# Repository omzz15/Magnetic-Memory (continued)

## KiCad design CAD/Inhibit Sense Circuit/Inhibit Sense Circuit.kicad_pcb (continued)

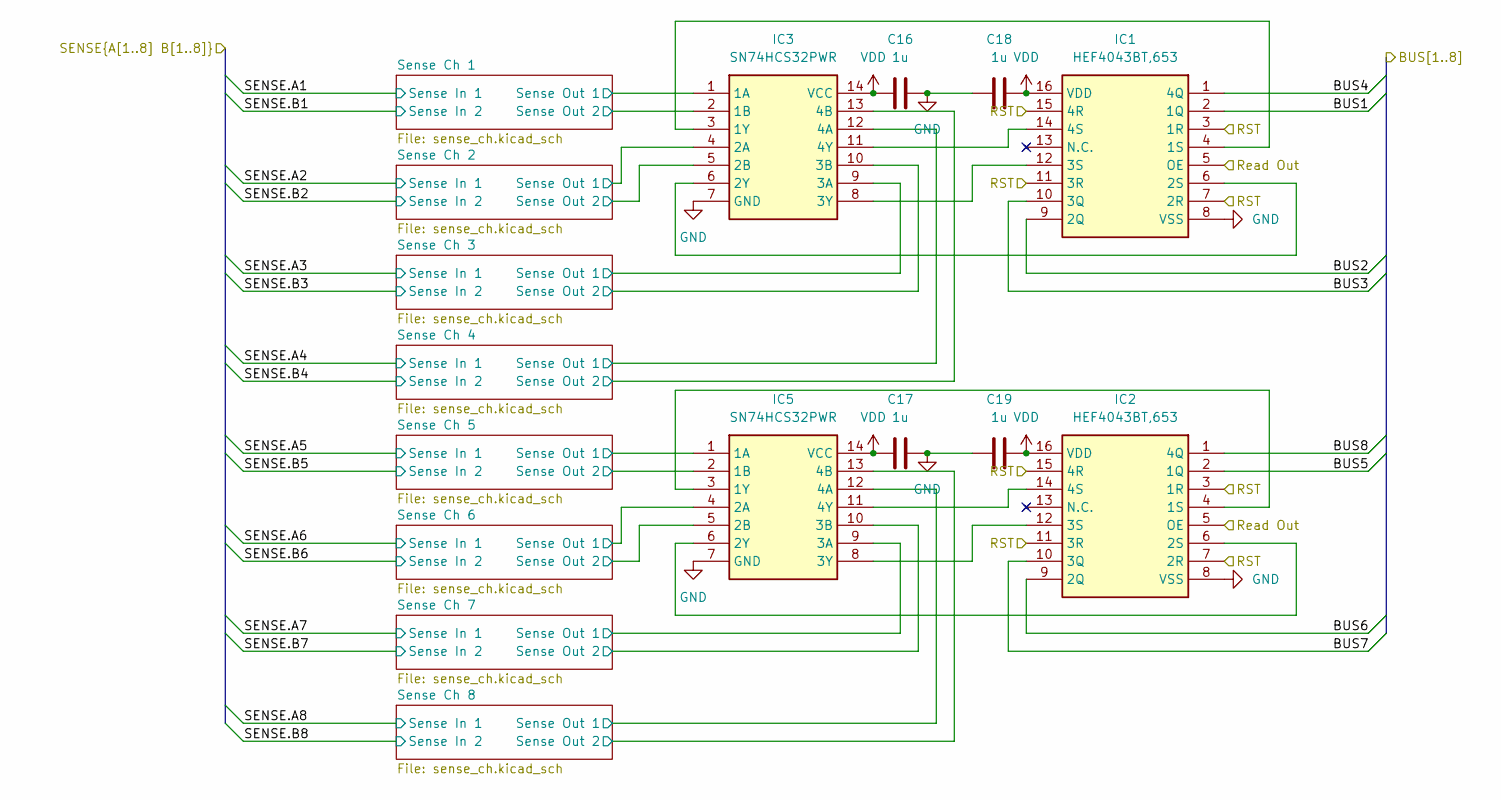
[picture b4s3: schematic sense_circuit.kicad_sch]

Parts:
C16, C17, C18, C19: 1u; C_0603_1608Metric_Pad1.08x0.95mm_HandSolder
IC1, IC2: HEF4043BT,653; HEF4043BT653; Mouser Part Number 771-HEF4043BT653
IC3, IC5: SN74HCS32PWR; SOP65P640X120-14N; Mouser Part Number 595-SN74HCS32PWR

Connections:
/BUS1: IC1.2 (1Q); also elsewhere on the board
/BUS2: IC1.9 (2Q); also elsewhere on the board
/BUS3: IC1.10 (3Q); also elsewhere on the board
/BUS4: IC1.1 (4Q); also elsewhere on the board
/BUS5: IC2.2 (1Q); also elsewhere on the board
/BUS6: IC2.9 (2Q); also elsewhere on the board
/BUS7: IC2.10 (3Q); also elsewhere on the board
/BUS8: IC2.1 (4Q); also elsewhere on the board
/RST: IC1.3 (1R), IC1.7 (2R), IC1.11 (3R), IC1.15 (4R), IC2.3 (1R), IC2.7 (2R), IC2.11 (3R), IC2.15 (4R); also elsewhere on the board
/Read Out: IC1.5 (OE), IC2.5 (OE); also elsewhere on the board
/Sense Circuit/Sense Ch 1/Sense Out 1: IC3.1 (1A); also elsewhere on the board
/Sense Circuit/Sense Ch 1/Sense Out 2: IC3.2 (1B); also elsewhere on the board
/Sense Circuit/Sense Ch 2/Sense Out 1: IC3.4 (2A); also elsewhere on the board
/Sense Circuit/Sense Ch 2/Sense Out 2: IC3.5 (2B); also elsewhere on the board
/Sense Circuit/Sense Ch 3/Sense Out 1: IC3.9 (3A); also elsewhere on the board
/Sense Circuit/Sense Ch 3/Sense Out 2: IC3.10 (3B); also elsewhere on the board
/Sense Circuit/Sense Ch 4/Sense Out 1: IC3.12 (4A); also elsewhere on the board
/Sense Circuit/Sense Ch 4/Sense Out 2: IC3.13 (4B); also elsewhere on the board
/Sense Circuit/Sense Ch 5/Sense Out 1: IC5.1 (1A); also elsewhere on the board
/Sense Circuit/Sense Ch 5/Sense Out 2: IC5.2 (1B); also elsewhere on the board
/Sense Circuit/Sense Ch 6/Sense Out 1: IC5.4 (2A); also elsewhere on the board
/Sense Circuit/Sense Ch 6/Sense Out 2: IC5.5 (2B); also elsewhere on the board
/Sense Circuit/Sense Ch 7/Sense Out 1: IC5.9 (3A); also elsewhere on the board
/Sense Circuit/Sense Ch 7/Sense Out 2: IC5.10 (3B); also elsewhere on the board
/Sense Circuit/Sense Ch 8/Sense Out 1: IC5.12 (4A); also elsewhere on the board
/Sense Circuit/Sense Ch 8/Sense Out 2: IC5.13 (4B); also elsewhere on the board
GND: C16.2, C17.2, C18.1, C19.1, IC1.8 (VSS), IC2.8 (VSS), IC3.7 (GND), IC5.7 (GND); also elsewhere on the board
unnamed: IC1.4 (1S), IC3.3 (1Y)
unnamed: IC1.6 (2S), IC3.6 (2Y)
unnamed: IC1.12 (3S), IC3.8 (3Y)
unnamed: IC1.14 (4S), IC3.11 (4Y)
unnamed: IC2.4 (1S), IC5.3 (1Y)
unnamed: IC2.6 (2S), IC5.6 (2Y)
unnamed: IC2.12 (3S), IC5.8 (3Y)
unnamed: IC2.14 (4S), IC5.11 (4Y)
VDD: C16.1, C17.1, C18.2, C19.2, IC1.16 (VDD), IC2.16 (VDD), IC3.14 (VCC), IC5.14 (VCC); also elsewhere on the board

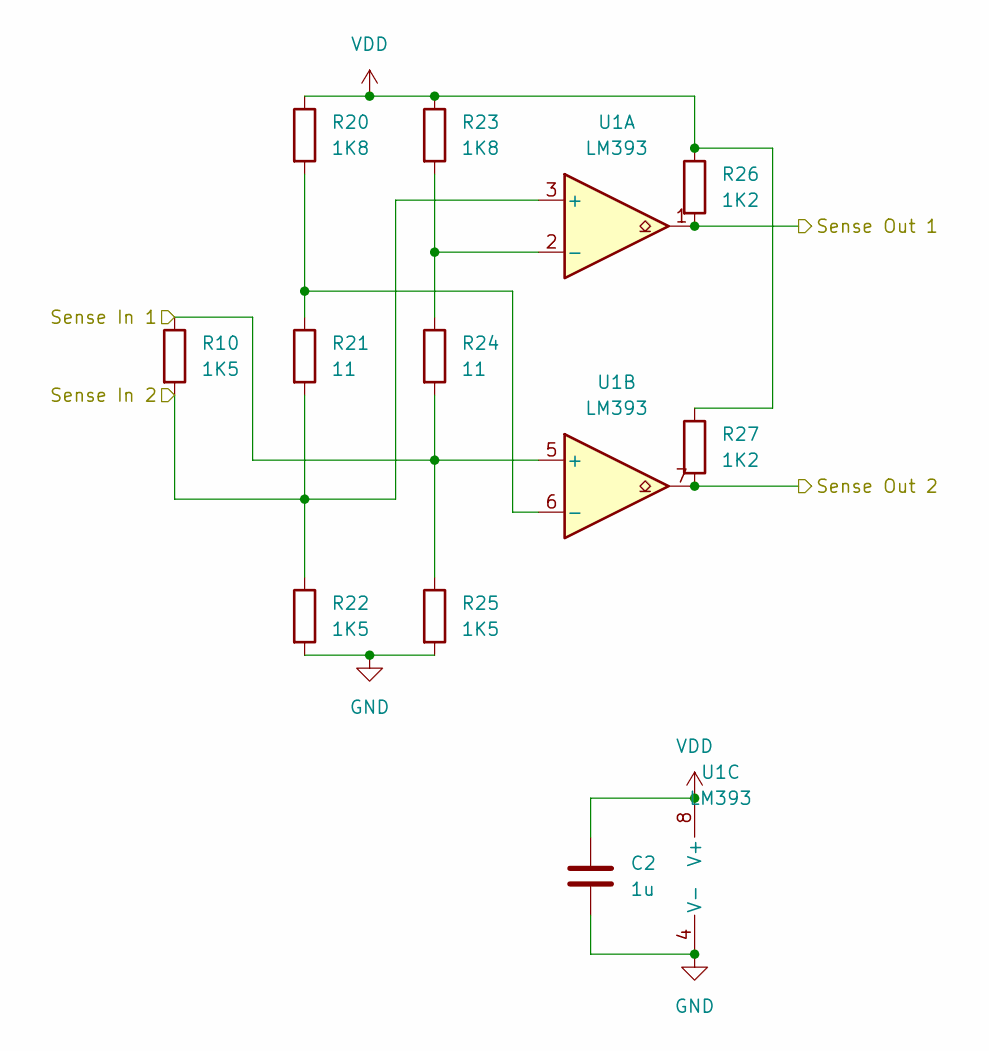
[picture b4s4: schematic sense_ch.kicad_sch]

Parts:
C2: 1u; C_0603_1608Metric_Pad1.08x0.95mm_HandSolder
R10, R22, R25: 1K5; R_0603_1608Metric_Pad0.98x0.95mm_HandSolder
R20, R23: 1K8; R_0603_1608Metric_Pad0.98x0.95mm_HandSolder
R21, R24: 11; R_0603_1608Metric_Pad0.98x0.95mm_HandSolder
R26, R27: 1K2; R_0603_1608Metric_Pad0.98x0.95mm_HandSolder
U1: LM393; SO1SOP-8-A_TPK

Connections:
/IS_LINES.A1: R10.1, R24.2, R25.1, U1.5 (+); also elsewhere on the board
/IS_LINES.B1: R10.2, R21.2, R22.1, U1.3 (+); also elsewhere on the board
/Sense Circuit/Sense Ch 1/Sense Out 1: R26.2, U1.1; also elsewhere on the board
/Sense Circuit/Sense Ch 1/Sense Out 2: R27.2, U1.7; also elsewhere on the board
GND: C2.2, R22.2, R25.2, U1.4 (V-); also elsewhere on the board
unnamed: R23.2, R24.1, U1.2 (-)
unnamed: R20.2, R21.1, U1.6 (-)
VDD: C2.1, R20.1, R23.1, R26.1, R27.1, U1.8 (V+); also elsewhere on the board

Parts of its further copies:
C1, C3, C4, C5, C6, C7, C8: 1u; C_0603_1608Metric_Pad1.08x0.95mm_HandSolder
R9, R13, R16, R19, R28, R31, R34, R37, R41, R47, R53, R57, R60, R63, R66, R69, R72, R75, R78, R83, R86: 1K5; R_0603_1608Metric_Pad0.98x0.95mm_HandSolder
R11, R14, R29, R32, R38, R43, R55, R58, R64, R67, R73, R76, R81, R84: 1K8; R_0603_1608Metric_Pad0.98x0.95mm_HandSolder
R12, R15, R30, R33, R39, R45, R56, R59, R65, R68, R74, R77, R82, R85: 11; R_0603_1608Metric_Pad0.98x0.95mm_HandSolder
R17, R18, R35, R36, R49, R51, R61, R62, R70, R71, R79, R80, R87, R88: 1K2; R_0603_1608Metric_Pad0.98x0.95mm_HandSolder
U2, U3, U4, U5, U6, U7, U8: LM393; SO1SOP-8-A_TPK

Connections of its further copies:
/IS_LINES.A2: R9.1, R15.2, R16.1, U2.5 (+); also elsewhere on the board
/IS_LINES.A3: R19.1, R33.2, R34.1, U3.5 (+); also elsewhere on the board
/IS_LINES.A4: R28.1, R45.2, R47.1, U4.5 (+); also elsewhere on the board
/IS_LINES.A5: R37.1, R59.2, R60.1, U5.5 (+); also elsewhere on the board
/IS_LINES.A6: R53.1, R68.2, R69.1, U6.5 (+); also elsewhere on the board
/IS_LINES.A7: R63.1, R77.2, R78.1, U7.5 (+); also elsewhere on the board
/IS_LINES.A8: R72.1, R85.2, R86.1, U8.5 (+); also elsewhere on the board
/IS_LINES.B2: R9.2, R12.2, R13.1, U2.3 (+); also elsewhere on the board
/IS_LINES.B3: R19.2, R30.2, R31.1, U3.3 (+); also elsewhere on the board
/IS_LINES.B4: R28.2, R39.2, R41.1, U4.3 (+); also elsewhere on the board
/IS_LINES.B5: R37.2, R56.2, R57.1, U5.3 (+); also elsewhere on the board
/IS_LINES.B6: R53.2, R65.2, R66.1, U6.3 (+); also elsewhere on the board
/IS_LINES.B7: R63.2, R74.2, R75.1, U7.3 (+); also elsewhere on the board
/IS_LINES.B8: R72.2, R82.2, R83.1, U8.3 (+); also elsewhere on the board
/Sense Circuit/Sense Ch 2/Sense Out 1: R17.2, U2.1; also elsewhere on the board
/Sense Circuit/Sense Ch 2/Sense Out 2: R18.2, U2.7; also elsewhere on the board
/Sense Circuit/Sense Ch 3/Sense Out 1: R35.2, U3.1; also elsewhere on the board
/Sense Circuit/Sense Ch 3/Sense Out 2: R36.2, U3.7; also elsewhere on the board
/Sense Circuit/Sense Ch 4/Sense Out 1: R49.2, U4.1; also elsewhere on the board
/Sense Circuit/Sense Ch 4/Sense Out 2: R51.2, U4.7; also elsewhere on the board
/Sense Circuit/Sense Ch 5/Sense Out 1: R61.2, U5.1; also elsewhere on the board
/Sense Circuit/Sense Ch 5/Sense Out 2: R62.2, U5.7; also elsewhere on the board
/Sense Circuit/Sense Ch 6/Sense Out 1: R70.2, U6.1; also elsewhere on the board
/Sense Circuit/Sense Ch 6/Sense Out 2: R71.2, U6.7; also elsewhere on the board
/Sense Circuit/Sense Ch 7/Sense Out 1: R79.2, U7.1; also elsewhere on the board
/Sense Circuit/Sense Ch 7/Sense Out 2: R80.2, U7.7; also elsewhere on the board
/Sense Circuit/Sense Ch 8/Sense Out 1: R87.2, U8.1; also elsewhere on the board
/Sense Circuit/Sense Ch 8/Sense Out 2: R88.2, U8.7; also elsewhere on the board
GND: C1.2, C3.2, C4.2, C5.2, C6.2, C7.2, C8.2, R13.2, R16.2, R31.2, R34.2, R41.2, R47.2, R57.2, R60.2, R66.2, R69.2, R75.2, R78.2, R83.2, R86.2, U2.4 (V-), U3.4 (V-), U4.4 (V-), U5.4 (V-), U6.4 (V-), U7.4 (V-), U8.4 (V-); also elsewhere on the board
unnamed: R14.2, R15.1, U2.2 (-)
unnamed: R11.2, R12.1, U2.6 (-)
unnamed: R32.2, R33.1, U3.2 (-)
unnamed: R29.2, R30.1, U3.6 (-)
unnamed: R43.2, R45.1, U4.2 (-)
unnamed: R38.2, R39.1, U4.6 (-)
unnamed: R58.2, R59.1, U5.2 (-)
unnamed: R55.2, R56.1, U5.6 (-)
unnamed: R67.2, R68.1, U6.2 (-)
unnamed: R64.2, R65.1, U6.6 (-)
unnamed: R76.2, R77.1, U7.2 (-)
unnamed: R73.2, R74.1, U7.6 (-)
unnamed: R84.2, R85.1, U8.2 (-)
unnamed: R81.2, R82.1, U8.6 (-)
VDD: C1.1, C3.1, C4.1, C5.1, C6.1, C7.1, C8.1, R11.1, R14.1, R17.1, R18.1, R29.1, R32.1, R35.1, R36.1, R38.1, R43.1, R49.1, R51.1, R55.1, R58.1, R61.1, R62.1, R64.1, R67.1, R70.1, R71.1, R73.1, R76.1, R79.1, R80.1, R81.1, R84.1, R87.1, R88.1, U2.8 (V+), U3.8 (V+), U4.8 (V+), U5.8 (V+), U6.8 (V+), U7.8 (V+), U8.8 (V+); also elsewhere on the board

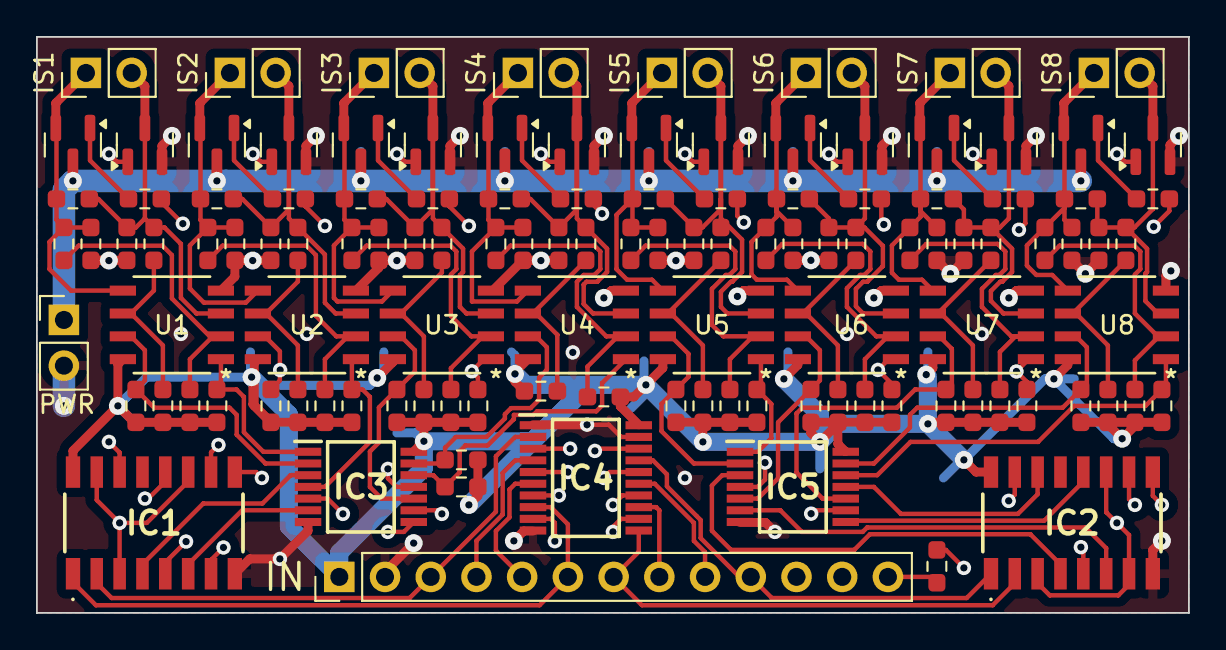
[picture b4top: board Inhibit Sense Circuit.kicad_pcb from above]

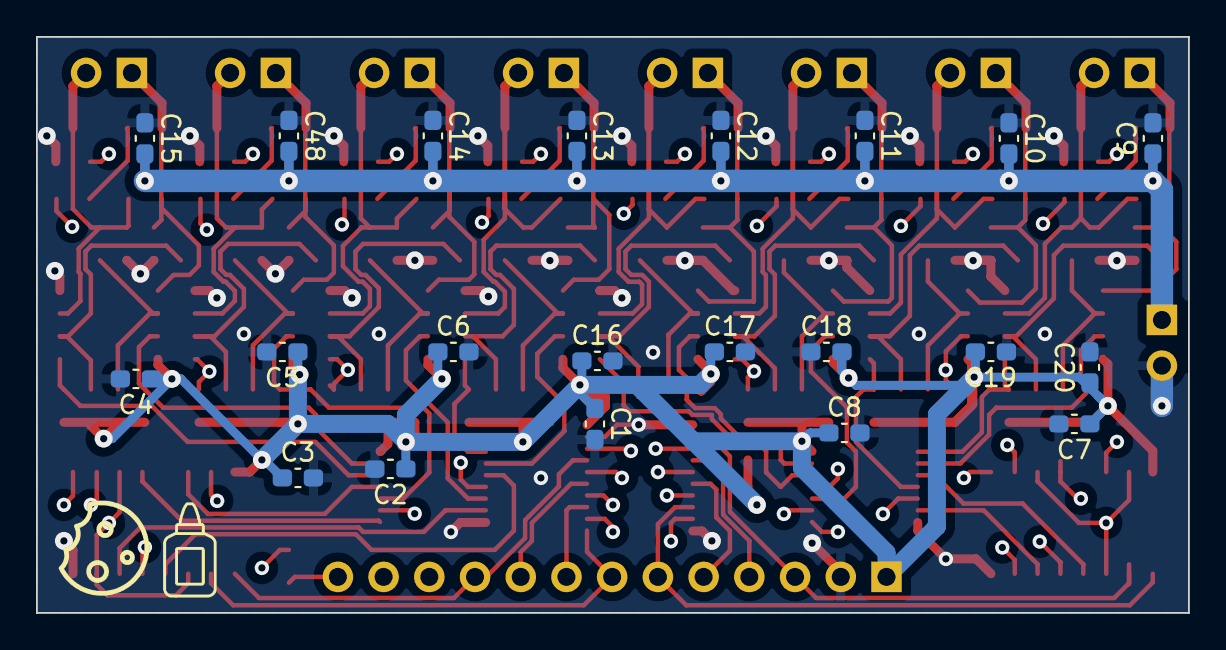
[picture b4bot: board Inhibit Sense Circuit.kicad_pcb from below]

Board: 4 copper layers, 64.0 x 32.0 mm, 141 parts (21 on the bottom side), 87 nets.

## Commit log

2024-01-24 refactored some things
2024-01-24 cleaned up some pulse code
2024-01-24 refactored and made the logic schematic more readable
2024-02-01 Updated Memory Logic Architecture
2024-02-02 updated architecture
2024-02-02 Revert "updated architecture"
    This reverts commit ca71a91292b383d21d315e699ec1a2562598e178.
2024-02-02 fixed merging and updated architecture
2024-02-02 Update file reference
2024-02-02 updated some stuff
2024-02-03 Worked on Part Selection
2024-02-17 updated prices
2024-02-17 updated comps
2026-04-25 working magnetic core memorygit add .
2026-04-25 cleaned up code
2026-04-25 updated stuff
2026-04-25 cleaned up repo
